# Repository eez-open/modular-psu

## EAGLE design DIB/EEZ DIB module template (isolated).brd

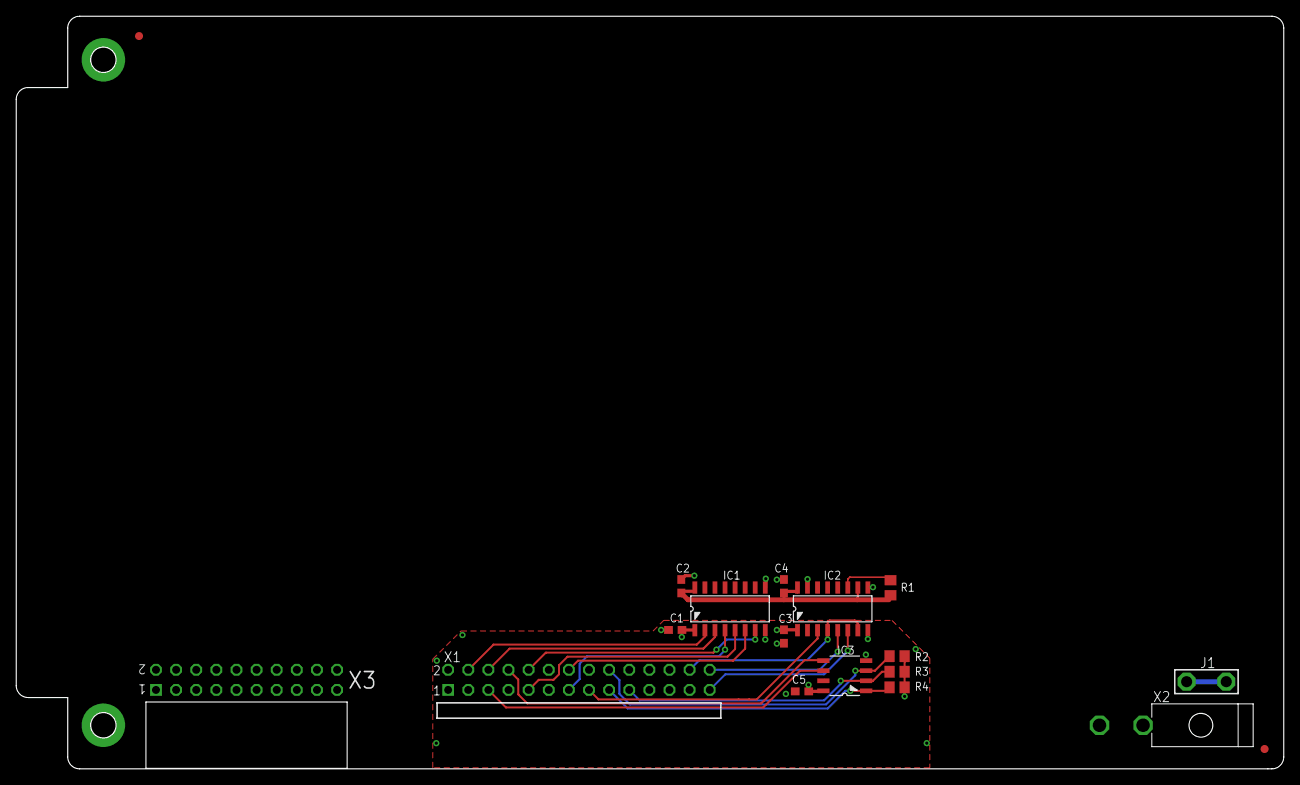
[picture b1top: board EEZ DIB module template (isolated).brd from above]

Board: 4 copper layers, 160.0 x 95.0 mm, 20 parts (0 on the bottom side), 21 nets.

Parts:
C1, C2, C3, C4, C5: 100n; C0603
FM1, FM2: FIDUCIAL_2; FIDUCIAL_DUAL
IC1: Si8662AB-B-IS1; SOIC-16
IC2: Si8641AB-B-IS1; SOIC-16
IC3: M24C32-WMN6P; SOIC127P600X173-8N
J1: 4907; PCB_TAB-4907
KK1, KK2: PMB-1; PCB-MB
R1, R2, R3, R4: 10K; R0805
X1: 77317-104-28LF
X2: 39-30-1020; MINIFIT_39301020
X3: ZL263-20DG; SSW-110-02-T-D-RA

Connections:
+3V3: C2.2, C4.2, IC1.16, IC2.10, IC2.16, R1.2
DIB_A0: IC3.1, R4.2, X1.17
DIB_A1: IC3.2, R3.2, X1.19
DIB_A2: IC3.3, R2.2, X1.18
DIB_BOOT0: IC2.4, IC2.7, X1.26
DIB_CSA: IC1.5, X1.9
DIB_IRQ: IC1.7, X1.10
DIB_MISO: IC1.6, X1.14
DIB_MOSI: IC2.3, X1.15
DIB_NRESET: IC1.2, X1.4
DIB_SCL: IC3.6, X1.5
DIB_SCLK: IC1.4, X1.13
DIB_SDA: IC3.5, X1.8
DIB_SYNC: IC1.3, X1.6
DIB_UART_RX: IC2.6, X1.27
DIB_UART_TX: IC2.5, X1.28
GND: C2.1, C4.1, IC1.9, IC2.9, IC2.15
GNDIO: C1.2, C3.2, C5.1, IC1.8, IC2.2, IC2.8, IC3.4, IC3.7, X1.7, X1.11, X1.16, X1.20, X1.25
PE: J1.1, J1.2
UART_TX: IC2.11, R1.1
V+: C1.1, C3.1, C5.2, IC1.1, IC2.1, IC3.8, R2.1, R3.1, R4.1, X1.1

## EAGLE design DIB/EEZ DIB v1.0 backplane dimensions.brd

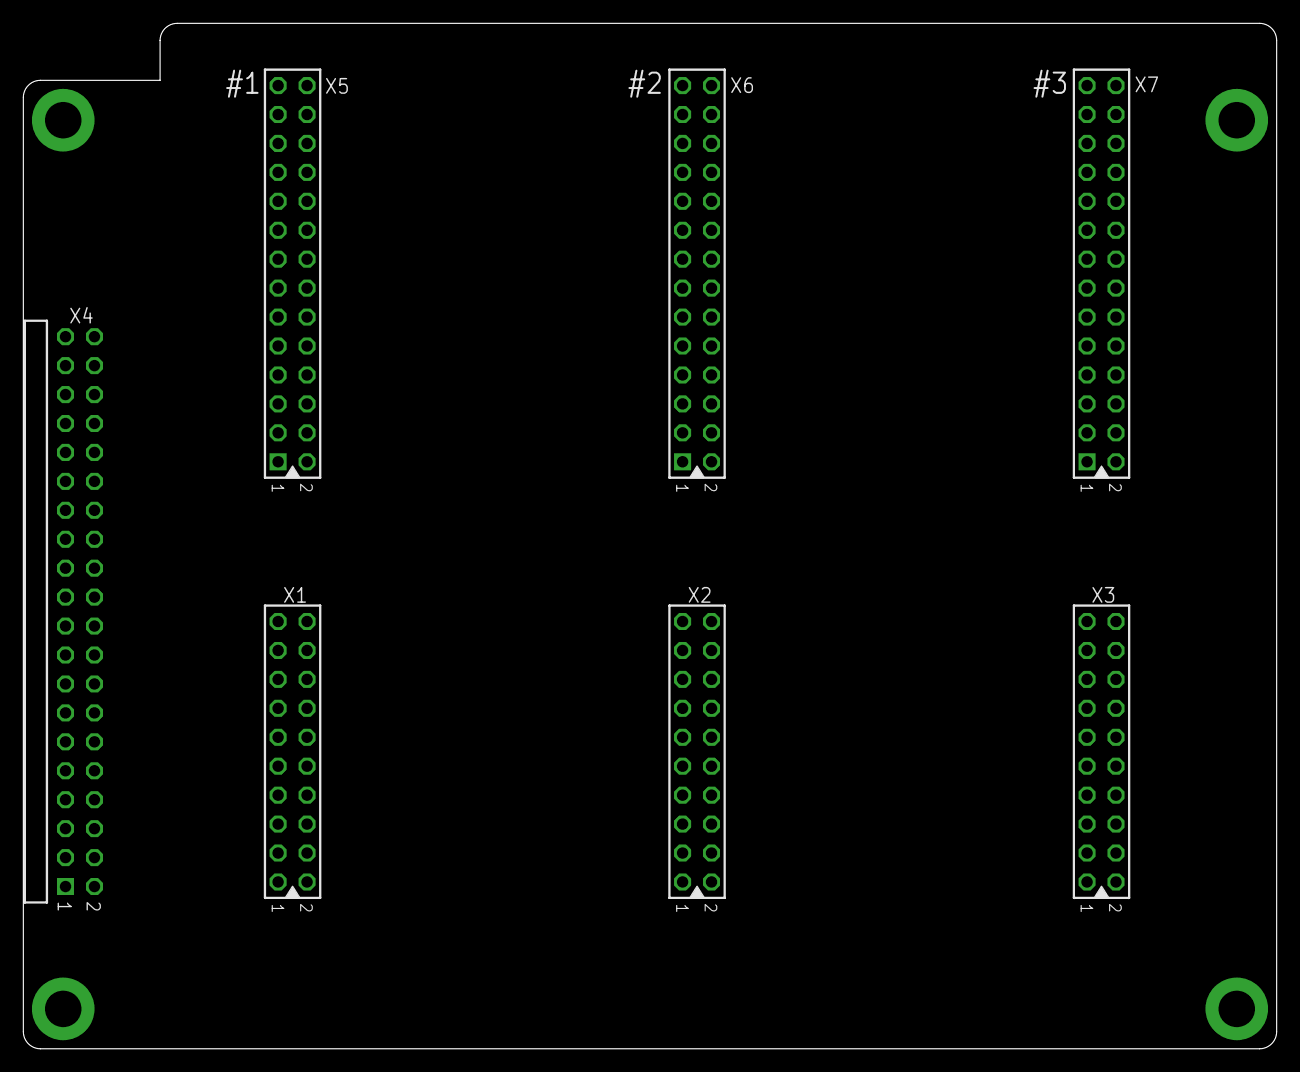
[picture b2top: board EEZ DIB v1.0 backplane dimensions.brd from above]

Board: 2 copper layers, 110.0 x 90.0 mm, 7 parts (0 on the bottom side), 12 nets, no tracks yet.

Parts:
X1, X2, X3: ZL202-20G; DS1021-2*10SF11
X4: ZL212-40KG
X5, X6, X7: TSW-114-07-F-D

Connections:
CH1_IN+: X1.6, X1.7, X1.8, X1.9, X1.10
CH1_OUT+: X1.1, X1.2, X1.3, X1.4, X1.5
CH2_OUT+: X2.1, X2.2, X2.3, X2.4, X2.5
CH3+: X3.1, X3.2, X3.3, X3.4, X3.5
CH3-: X3.16, X3.17, X3.18, X3.19, X3.20
unnamed: X2.16, X2.17, X2.18, X2.19, X2.20
unnamed: X3.6, X3.7, X3.8, X3.9, X3.10
unnamed: X3.11, X3.12, X3.13, X3.14, X3.15
unnamed: X1.16, X1.17, X1.18, X1.19, X1.20
unnamed: X1.11, X1.12, X1.13, X1.14, X1.15
unnamed: X2.11, X2.12, X2.13, X2.14, X2.15
unnamed: X2.6, X2.7, X2.8, X2.9, X2.10

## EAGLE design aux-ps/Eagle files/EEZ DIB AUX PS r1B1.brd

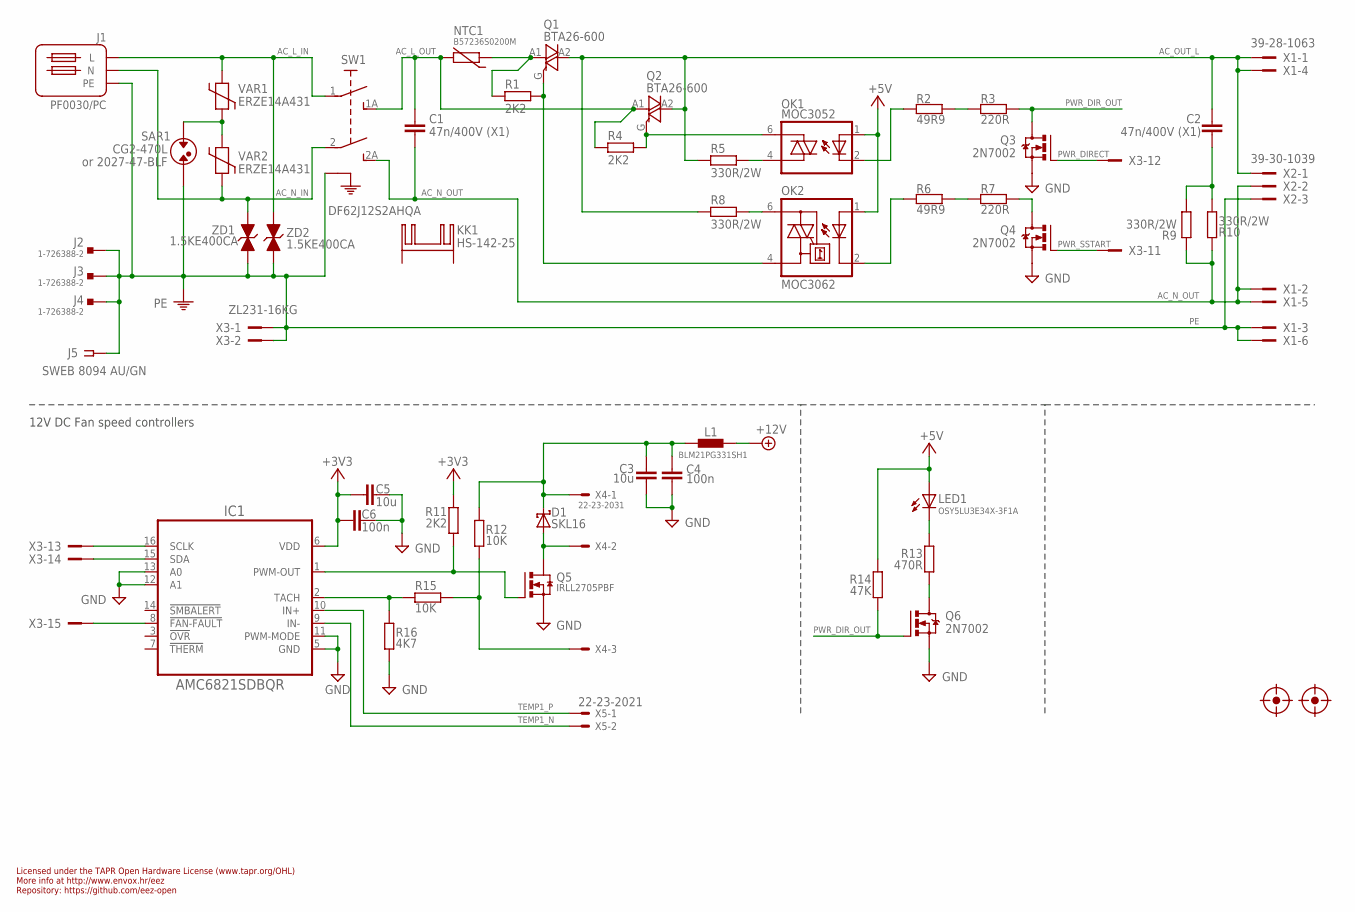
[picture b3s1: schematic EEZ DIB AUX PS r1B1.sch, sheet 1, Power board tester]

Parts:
C1, C2: 47n/400V (X1); C102-054X133
C3, C5: 10u; C1206
C4, C6: 100n; C0603
D1: SKL16; SOD123
FM1, FM2: FIDUCIAL
IC1: AMC6821SDBQR; DBQ16
J1: PF0030/PC
J2, J3, J4: 1-726388-2; PCB_TAB-4.8MM
J5: SWEB 8094 AU/GN; S16N-PC
KK1: HS-142-25; SK129
L1: BLM21PG331SH1; 0805
LED1: OSY5LU3E34X-3F1A; OSG8
NTC1: B57236S0200M; NTC_11.5X6_RM5
OK1: MOC3052; DIL6-SMD
OK2: MOC3062; DIL6-SMD; MPN MOC3033S-M
Q1, Q2: BTA26-600; TOP3S-1
Q3, Q4: 2N7002; SOT103P240X110-3N
Q5: IRLL2705PBF; SOT223
Q6: 2N7002; SOT103P240X110-3N; MPN 2N7002-7-F
R1, R4, R11: 2K2; R0805
R2, R6: 49R9; R0805
R3, R7: 220R; R0805
R5, R8, R9, R10: 330R/2W; R2512
R12, R15: 10K; R0805
R13: 470R; R0805
R14: 47K; R0805
R16: 4K7; R0805
SAR1: CG2-470L; SAR
SW1: DF62J12S2AHQA; DF62J12S2
VAR1, VAR2: ERZE14A431; VARISTOR_13MM
X1: 39-28-1063; MINIFIT_5566-06A_CRE
X2: 39-30-1039; MINIFIT_39301039_CRE
X3: ZL231-16KG; ML16L
X4: 22-23-2031
X5: 22-23-2021
ZD1, ZD2: 1.5KE400CA; DO201-BIDIR

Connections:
+3V3: C5.2, C6.2, IC1.6 (VDD), R11.1; also elsewhere on the board
+5V: LED1.A, OK1.1 (A), OK2.1 (A), R14.1; also elsewhere on the board
+12V: L1.2; also elsewhere on the board
AC_L_IN: J1.L, SW1.1, VAR1.2, ZD2.A (2)
AC_L_OUT: C1.1, NTC1.1, Q2.A1, R4.2, SW1.1A (S); also elsewhere on the board
AC_N_IN: J1.N, SW1.2 (P1), VAR2.1, ZD1.A (2)
AC_N_OUT: C1.2, R9.1, R10.1, SW1.2A (S1), X1.2, X1.5, X2.2; also elsewhere on the board
AC_OUT_L: C2.1, Q1.A2, Q2.A2, R5.2, R8.2, X1.1, X1.4, X2.1
FAN_OUT: D1.A, Q5.2 (D), Q5.4 (D), X4.2
FAN_SENSE: R12.1, R15.2, X4.3
unnamed: NTC1.2, Q1.A1, R1.1
unnamed: IC1.2 (TACH), R15.1, R16.1
unnamed: SAR1.P$1, VAR1.1, VAR2.2
unnamed: Q6.3 (D), R13.2
unnamed: LED1.C, R13.1
unnamed: Q4.3 (D), R7.2
unnamed: IC1.1 (PWM-OUT), Q5.1 (G), R11.2
unnamed: C3.1, C4.1, D1.C, L1.1, R12.2, X4.1
unnamed: OK1.6 (A2), Q2.G, R4.1
unnamed: OK2.4 (A1), Q1.G, R1.2
unnamed: OK2.6 (A2), R8.1
unnamed: R2.2, R3.1
unnamed: R6.2, R7.1
unnamed: OK1.4 (A1), R5.1
unnamed: C2.2, R9.2, R10.2
unnamed: OK2.2 (C), R6.1
unnamed: OK1.2 (C), R2.1
NFAULT: IC1.8 (!FAN-FAULT), X3.15
PE: J1.PE, J2.P$1, J2.P$2, J3.P$1, J3.P$2, J4.P$1, J4.P$2, J5.1, J5.NC1, J5.NC2, J5.NC3, J5.NC4, SAR1.P$2, SW1.PE1 (PE), SW1.PE2 (PE), X1.3, X1.6, X2.3, X3.1, X3.2, ZD1.C (1), ZD2.C (1); also elsewhere on the board
PWR_DIRECT: Q3.1 (G), X3.12
PWR_DIR_OUT: Q3.3 (D), Q6.1 (G), R3.2, R14.2
PWR_SSTART: Q4.1 (G), X3.11
SSCL: IC1.16 (SCLK), X3.13
SSDA: IC1.15 (SDA), X3.14
TEMP1_N: IC1.9 (IN-), X5.2
TEMP1_P: IC1.10 (IN+), X5.1

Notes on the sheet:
Licensed under the TAPR Open Hardware License (www.tapr.org/OHL)
Repository: https://github.com/eez-open
More info at http://www.envox.hr/eez
or 2027-47-BLF
12V DC Fan speed controllers

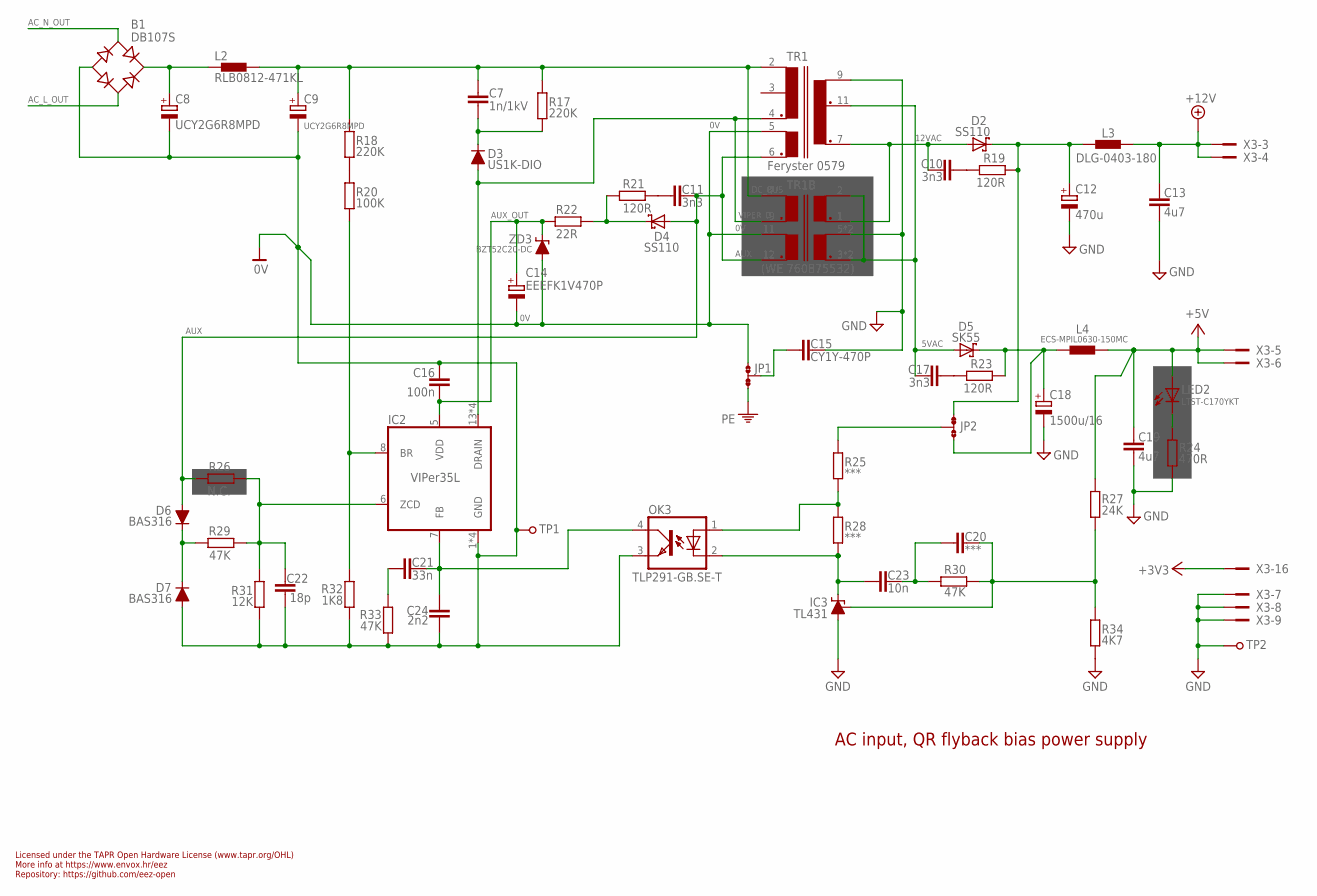
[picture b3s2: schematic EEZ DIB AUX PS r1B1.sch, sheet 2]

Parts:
B1: DB107S; DBS
C7: 1n/1kV; C1210
C8, C9: UCY2G6R8MPD; ECAP5/10.5
C10, C11, C17: 3n3; C0805
C12: 470u; ECAP5/10.5
C13, C19: 4u7; C1206
C14: EEEFK1V470P; CAPAE660X610N
C15: CY1Y-470P; CY075-032X103
C16: 100n; C0603
C18: 1500u/16; ECAP5/13
C20: ***; C0805
C21: 33n; C0805
C22: 18p; C0603
C23: 10n; C0805
C24: 2n2; C0805
D2, D4: SS110; SMB
D3: US1K-DIO; DO214AA
D5: SK55; SMB
D6, D7: BAS316; SOD323-R
IC2: VIPer35L; SOIC-16
IC3: TL431; SOT103P240X110-3N
JP1, JP2: JP3-CUT
L2: RLB0812-471KL; FERSYTER_DSZ6
L3: DLG-0403-180; DE0403
L4: ECS-MPIL0630-150MC; DE0704
LED2: LTST-C170YKT; LED_0805
OK3: TLP291-GB.SE-T; SO4
R17, R18: 220K; R1206
R19, R21, R23: 120R; R0805
R20: 100K; R0805
R22: 22R; R0805
R24: 470R; R0805
R25, R28: ***; R0805
R26: N.C.; R0805
R27: 24K; R0805
R29, R30, R33: 47K; R0805
R31: 12K; R0805
R32: 1K8; R0805
R34: 4K7; R0805
TP1, TP2: PCB_TEST_TABSHIELD; PCB_SHIELD_TAB
TR1: Feryster 0579; FERYSTER_0579
TR1B: (WE 760875532); WE-UOST
X3: ZL231-16KG; ML16L
ZD3: BZT52C20-DC; SOD123

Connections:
5VAC: C17.2, D5.A, TR1.11 (S1_DOT), TR1B.2 (S1), TR1B.3 (S2_DOT), TR1B.4 (S2_DOT)
12VAC: C10.2, D2.A, TR1.7 (S2_DOT), TR1B.1 (S1_DOT)
+3V3: X3.16; also elsewhere on the board
+5V: C19.1, L4.2, LED2.A, R27.2, X3.5, X3.6; also elsewhere on the board
+5V_REC: C18.+, D5.C, JP2.NO, L4.1, R23.1
+12V: C13.1, L3.2, X3.3, X3.4; also elsewhere on the board
+12V_REC: C12.+, D2.C, JP2.NC, L3.1, R19.1
AC_L_OUT: B1.AC2; also elsewhere on the board
AC_N_OUT: B1.AC1; also elsewhere on the board
AUX: C11.2, D4.A, D6.A, R26.2, TR1.6 (AUX_DOT), TR1B.12 (AUX_DOT)
AUX_OUT: C14.1 (+), C16.2, IC2.5 (VDD), R22.2, ZD3.C
AUX_REC: D4.C, R21.1, R22.1
DC_BUS: C7.1, C9.+, L2.P$2 (2), R17.1, R18.1, TR1.2 (P1), TR1B.7 (P1)
FB1: C23.1, IC3.1 (C), OK3.2 (C), R28.2
unnamed: C15.1, JP1.COM
unnamed: OK3.1 (A), R25.2, R28.1
unnamed: C10.1, R19.2
unnamed: B1.+, C8.+, L2.P$1 (1)
unnamed: LED2.C, R24.1
unnamed: JP2.COM, R25.1
unnamed: IC2.8 (BR), R20.2, R32.1
unnamed: R18.2, R20.1
unnamed: C7.2, D3.C, R17.2
unnamed: C21.2, C24.1, IC2.7 (FB), OK3.4 (COL)
unnamed: C11.1, R21.2
unnamed: C22.1, IC2.6 (ZCD), R26.1, R29.1, R31.2
unnamed: C17.1, R23.2
unnamed: C20.2, IC3.2 (REF), R27.1, R30.2, R34.2
unnamed: C20.1, C23.2, R30.1
unnamed: C21.1, R33.1
unnamed: D6.C, D7.C, R29.2
PE: JP1.NC; also elsewhere on the board

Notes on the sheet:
Licensed under the TAPR Open Hardware License (www.tapr.org/OHL)
Repository: https://github.com/eez-open
More info at https://www.envox.hr/eez
AC input, QR flyback bias power supply

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
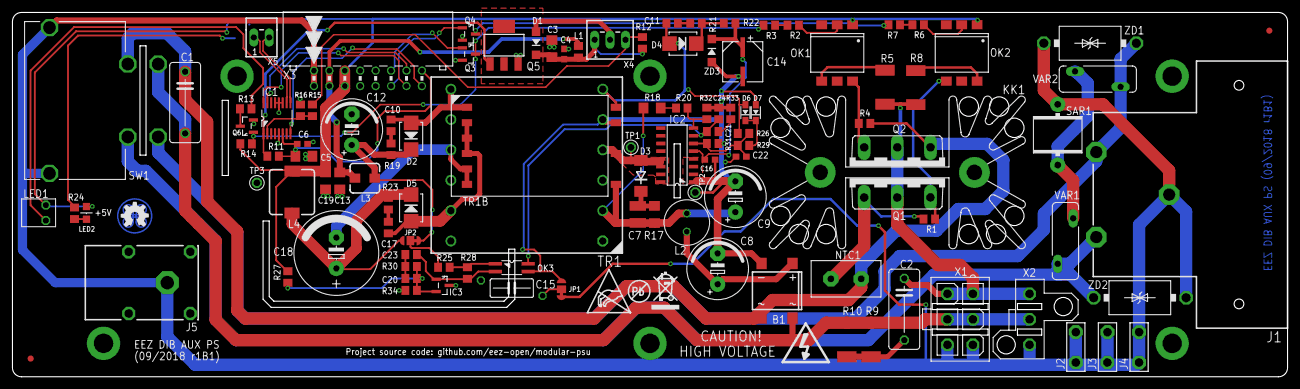
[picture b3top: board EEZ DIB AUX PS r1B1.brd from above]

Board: 2 copper layers, 210.0 x 60.0 mm, 116 parts (0 on the bottom side), 65 nets.

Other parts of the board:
EEZ_SIGNATURE: SIGNATURESMALL; SIGNATURE_5MM
TP3: PCB_SHIELD_TAB
U$2: PB_SMALL
U$3: RECYCLE_BIN1/8
U$4: ESD_SYMBOL

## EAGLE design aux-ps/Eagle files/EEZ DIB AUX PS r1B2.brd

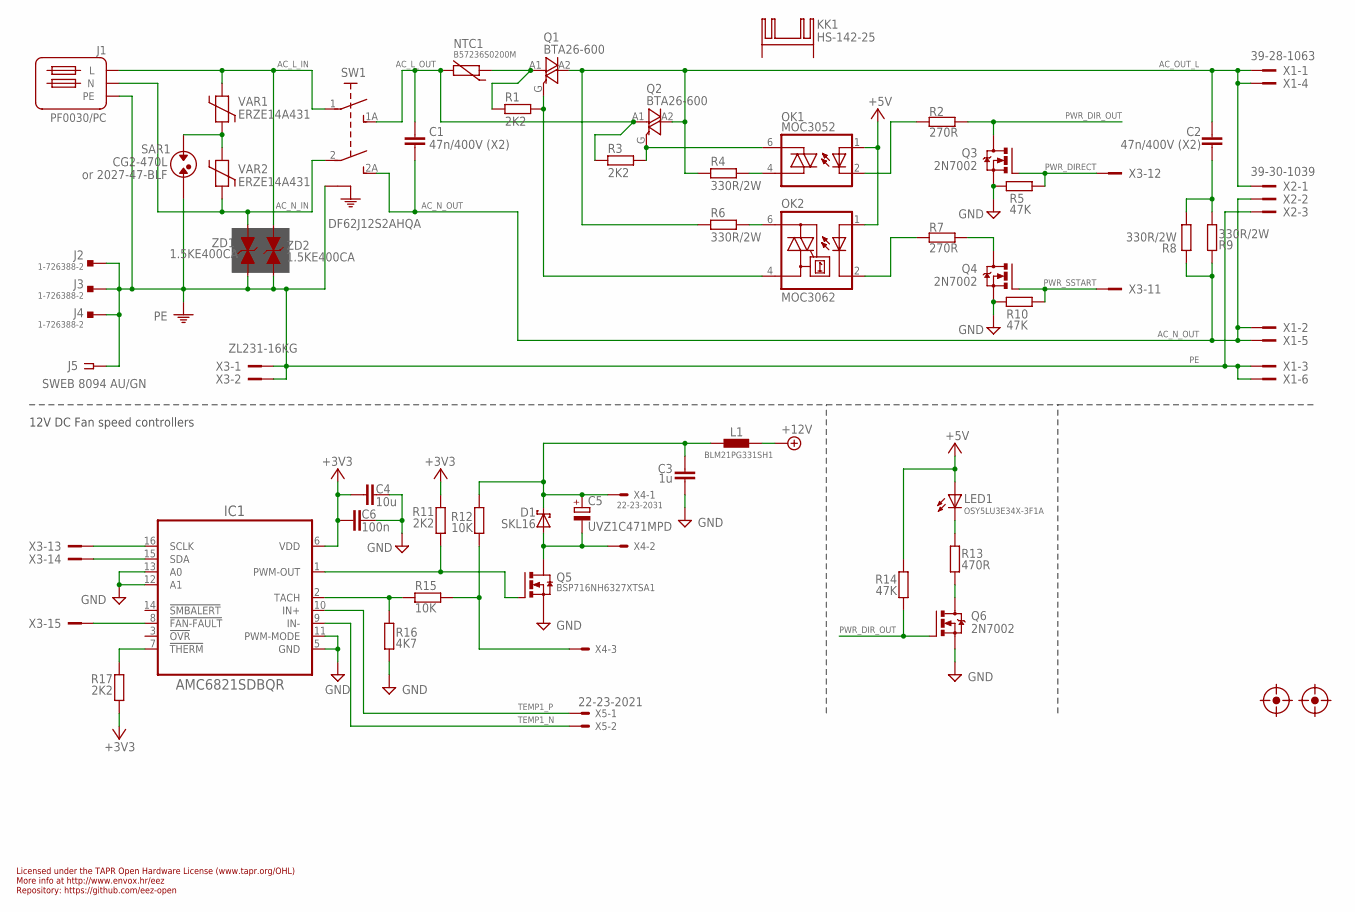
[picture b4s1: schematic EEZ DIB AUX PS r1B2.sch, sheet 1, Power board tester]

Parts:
C1, C2: 47n/400V (X2); C102-054X133
C3: 1u; C0805
C4: 10u; C1206
C5: UVZ1C471MPD; ECAP3.5/8
C6: 100n; C0603
D1: SKL16; SOD123
FM1, FM2: FIDUCIAL
IC1: AMC6821SDBQR; DBQ16
J1: PF0030/PC
J2, J3, J4: 1-726388-2; PCB_TAB-4.8MM
J5: SWEB 8094 AU/GN; S16N-PC
KK1: HS-142-25; SK129
L1: BLM21PG331SH1; 0805
LED1: OSY5LU3E34X-3F1A; OSG8
NTC1: B57236S0200M; NTC_11.5X6_RM5
OK1: MOC3052; DIL6-SMD
OK2: MOC3062; DIL6-SMD; MPN MOC3033S-M
Q1, Q2: BTA26-600; TOP3S-1
Q3, Q4: 2N7002; SOT103P240X110-3N
Q5: BSP716NH6327XTSA1; SOT223
Q6: 2N7002; SOT103P240X110-3N; MPN 2N7002-7-F
R1, R3, R11, R17: 2K2; R0805
R2, R7: 270R; R0805
R4, R6, R8, R9: 330R/2W; R2512
R5, R10, R14: 47K; R0805
R12, R15: 10K; R0805
R13: 470R; R0805
R16: 4K7; R0805
SAR1: CG2-470L; SAR
SW1: DF62J12S2AHQA; DF62J12S2
VAR1, VAR2: ERZE14A431; VARISTOR_13MM
X1: 39-28-1063; MINIFIT_5566-06A_CRE
X2: 39-30-1039; MINIFIT_39301039_CRE
X3: ZL231-16KG; ML16L
X4: 22-23-2031
X5: 22-23-2021
ZD1, ZD2: 1.5KE400CA; DO201-BIDIR

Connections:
+3V3: C4.2, C6.2, IC1.6 (VDD), R11.1, R17.2; also elsewhere on the board
+5V: LED1.A, OK1.1 (A), OK2.1 (A), R14.1; also elsewhere on the board
+12V: L1.2; also elsewhere on the board
+12V_FAN: C3.1, C5.+, D1.C, L1.1, R12.2, X4.1
AC_L_IN: J1.L, SW1.1, VAR1.2, ZD2.A (2)
AC_L_OUT: C1.1, NTC1.1, Q2.A1, R3.2, SW1.1A (S); also elsewhere on the board
AC_N_IN: J1.N, SW1.2 (P1), VAR2.1, ZD1.A (2)
AC_N_OUT: C1.2, R8.1, R9.1, SW1.2A (S1), X1.2, X1.5, X2.2; also elsewhere on the board
AC_OUT_L: C2.1, Q1.A2, Q2.A2, R4.2, R6.2, X1.1, X1.4, X2.1
FAN_OUT: C5.-, D1.A, Q5.2 (D), Q5.4 (D), X4.2
FAN_SENSE: R12.1, R15.2, X4.3
GND: C3.2, C4.1, C6.1, IC1.5 (GND), IC1.11 (PWM-MODE), IC1.12 (A1), IC1.13 (A0), Q3.2 (S), Q4.2 (S), Q5.3 (S), Q6.2 (S), R5.1, R10.1, R16.2; also elsewhere on the board
unnamed: NTC1.2, Q1.A1, R1.1
unnamed: IC1.2 (TACH), R15.1, R16.1
unnamed: IC1.7 (!THERM), R17.1
unnamed: SAR1.P$1, VAR1.1, VAR2.2
unnamed: OK2.2 (C), R7.1
unnamed: OK1.2 (C), R2.1
unnamed: Q6.3 (D), R13.2
unnamed: LED1.C, R13.1
unnamed: Q4.3 (D), R7.2
unnamed: IC1.1 (PWM-OUT), Q5.1 (G), R11.2
unnamed: OK1.6 (A2), Q2.G, R3.1
unnamed: OK2.4 (A1), Q1.G, R1.2
unnamed: OK2.6 (A2), R6.1
unnamed: OK1.4 (A1), R4.1
unnamed: C2.2, R8.2, R9.2
NFAULT: IC1.8 (!FAN-FAULT), X3.15
PE: J1.PE, J2.P$1, J2.P$2, J3.P$1, J3.P$2, J4.P$1, J4.P$2, J5.1, J5.NC1, J5.NC2, J5.NC3, J5.NC4, SAR1.P$2, SW1.PE1 (PE), SW1.PE2 (PE), X1.3, X1.6, X2.3, X3.1, X3.2, ZD1.C (1), ZD2.C (1); also elsewhere on the board
PWR_DIRECT: Q3.1 (G), R5.2, X3.12
PWR_DIR_OUT: Q3.3 (D), Q6.1 (G), R2.2, R14.2
PWR_SSTART: Q4.1 (G), R10.2, X3.11
SSCL: IC1.16 (SCLK), X3.13
SSDA: IC1.15 (SDA), X3.14
TEMP1_N: IC1.9 (IN-), X5.2
TEMP1_P: IC1.10 (IN+), X5.1

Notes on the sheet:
Licensed under the TAPR Open Hardware License (www.tapr.org/OHL)
Repository: https://github.com/eez-open
More info at http://www.envox.hr/eez
or 2027-47-BLF
12V DC Fan speed controllers

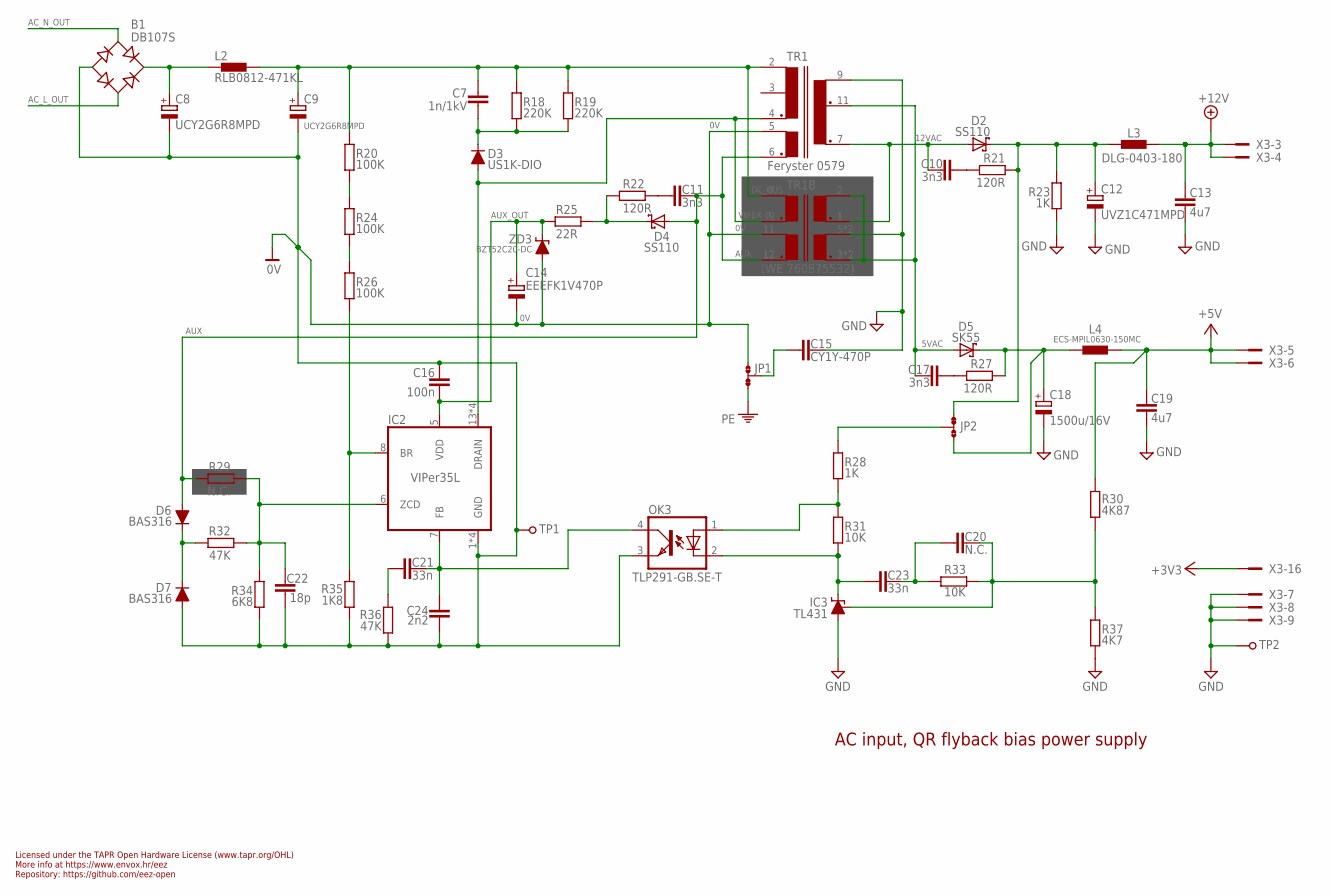
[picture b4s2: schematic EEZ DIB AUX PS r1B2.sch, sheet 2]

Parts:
B1: DB107S; DBS
C7: 1n/1kV; C1210
C8, C9: UCY2G6R8MPD; ECAP5/10.5
C10, C11, C17: 3n3; C0805
C12: UVZ1C471MPD; ECAP3.5/8
C13, C19: 4u7; C1210
C14: EEEFK1V470P; CAPAE660X610N
C15: CY1Y-470P; CY075-032X103
C16: 100n; C0603
C18: 1500u/16V; ECAP5/13
C20: N.C.; C0805
C21, C23: 33n; C0805
C22: 18p; C0603
C24: 2n2; C0805
D2, D4: SS110; SMB
D3: US1K-DIO; DO214AA
D5: SK55; SMB
D6, D7: BAS316; SOD323-R
IC2: VIPer35L; SOIC-16
IC3: TL431; SOT103P240X110-3N
JP1, JP2: JP3-CUT
L2: RLB0812-471KL; FERSYTER_DSZ6
L3: DLG-0403-180; DE0403
L4: ECS-MPIL0630-150MC; DE0704
OK3: TLP291-GB.SE-T; SO4
R18, R19: 220K; R1206
R20, R24, R26: 100K; R1206
R21, R22, R27: 120R; R0805
R23, R28: 1K; R0805
R25: 22R; R0805
R29: N.C.; R0805
R30: 4K87; R0805
R31, R33: 10K; R0805
R32, R36: 47K; R0805
R34: 6K8; R0805
R35: 1K8; R0805
R37: 4K7; R0805
TP1, TP2: PCB_TEST_TABSHIELD; PCB_SHIELD_TAB
TR1: Feryster 0579; FERYSTER_0579
TR1B: (WE 760875532); WE-UOST
X3: ZL231-16KG; ML16L
ZD3: BZT52C20-DC; SOD123

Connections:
0V: B1.-, C8.-, C9.-, C14.2 (-), C16.1, C22.2, C24.2, D7.A, IC2.1 (GND), IC2.2 (GND), IC2.3 (GND), IC2.4 (GND), JP1.NO, OK3.3 (EMIT), R34.1, R35.2, R36.2, TP1.1, TR1.5 (AUX), TR1B.11 (AUX), ZD3.A
5VAC: C17.2, D5.A, TR1.11 (S1_DOT), TR1B.2 (S1), TR1B.3 (S2_DOT), TR1B.4 (S2_DOT)
12VAC: C10.2, D2.A, TR1.7 (S2_DOT), TR1B.1 (S1_DOT)
+3V3: X3.16; also elsewhere on the board
+5V: C19.1, L4.2, R30.2, X3.5, X3.6; also elsewhere on the board
+5V_REC: C18.+, D5.C, JP2.NO, L4.1, R27.1
+12V: C13.1, L3.2, X3.3, X3.4; also elsewhere on the board
+12V_REC: C12.+, D2.C, JP2.NC, L3.1, R21.1, R23.1
AC_L_OUT: B1.AC2; also elsewhere on the board
AC_N_OUT: B1.AC1; also elsewhere on the board
AUX: C11.2, D4.A, D6.A, R29.2, TR1.6 (AUX_DOT), TR1B.12 (AUX_DOT)
AUX_OUT: C14.1 (+), C16.2, IC2.5 (VDD), R25.2, ZD3.C
AUX_REC: D4.C, R22.1, R25.1
DC_BUS: C7.1, C9.+, L2.P$2 (2), R18.1, R19.1, R20.1, TR1.2 (P1), TR1B.7 (P1)
FB1: C23.1, IC3.1 (C), OK3.2 (C), R31.2
GND: C12.-, C13.2, C15.2, C18.-, C19.2, IC3.3 (A), R23.2, R37.1, TP2.1, TR1.9 (S_COMM), TR1B.5 (S2), TR1B.6 (S2), X3.7, X3.8, X3.9; also elsewhere on the board
unnamed: C15.1, JP1.COM
unnamed: OK3.1 (A), R28.2, R31.1
unnamed: C10.1, R21.2
unnamed: B1.+, C8.+, L2.P$1 (1)
unnamed: R24.2, R26.1
unnamed: JP2.COM, R28.1
unnamed: IC2.8 (BR), R26.2, R35.1
unnamed: R20.2, R24.1
unnamed: C7.2, D3.C, R18.2, R19.2
unnamed: C21.2, C24.1, IC2.7 (FB), OK3.4 (COL)
unnamed: C11.1, R22.2
unnamed: C22.1, IC2.6 (ZCD), R29.1, R32.1, R34.2
unnamed: C17.1, R27.2
unnamed: C20.2, IC3.2 (REF), R30.1, R33.2, R37.2
unnamed: C20.1, C23.2, R33.1
unnamed: C21.1, R36.1
unnamed: D6.C, D7.C, R32.2
PE: JP1.NC; also elsewhere on the board
VIPER_D: D3.A, IC2.13 (DRAIN), IC2.14 (DRAIN), IC2.15 (DRAIN), IC2.16 (DRAIN), TR1.4 (P1_DOT), TR1B.9 (P1_DOT)

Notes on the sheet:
Licensed under the TAPR Open Hardware License (www.tapr.org/OHL)
Repository: https://github.com/eez-open
More info at https://www.envox.hr/eez
AC input, QR flyback bias power supply

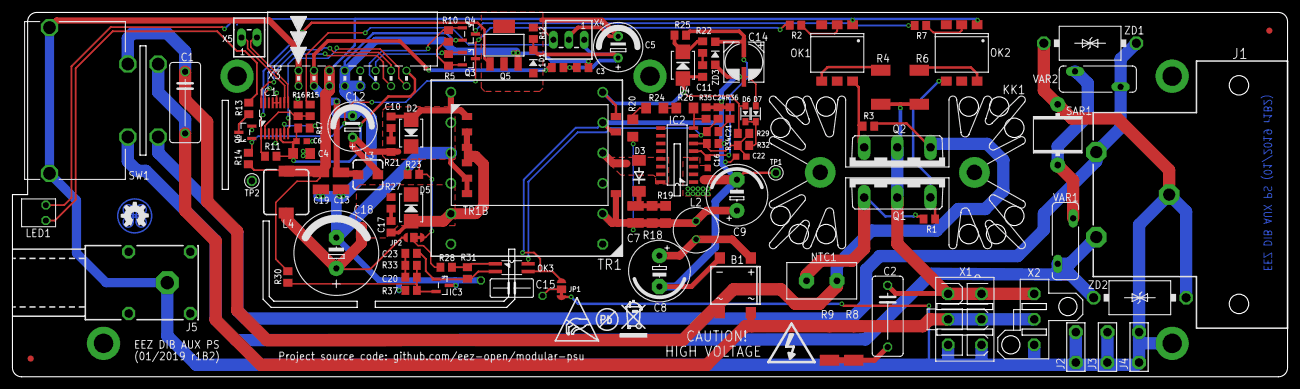
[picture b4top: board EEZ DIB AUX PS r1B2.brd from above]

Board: 2 copper layers, 210.0 x 60.0 mm, 117 parts (0 on the bottom side), 64 nets.

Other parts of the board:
EEZ_SIGNATURE: SIGNATURESMALL; SIGNATURE_5MM
U$2: PB_SMALL
U$3: RECYCLE_BIN1/8
U$4: ESD_SYMBOL

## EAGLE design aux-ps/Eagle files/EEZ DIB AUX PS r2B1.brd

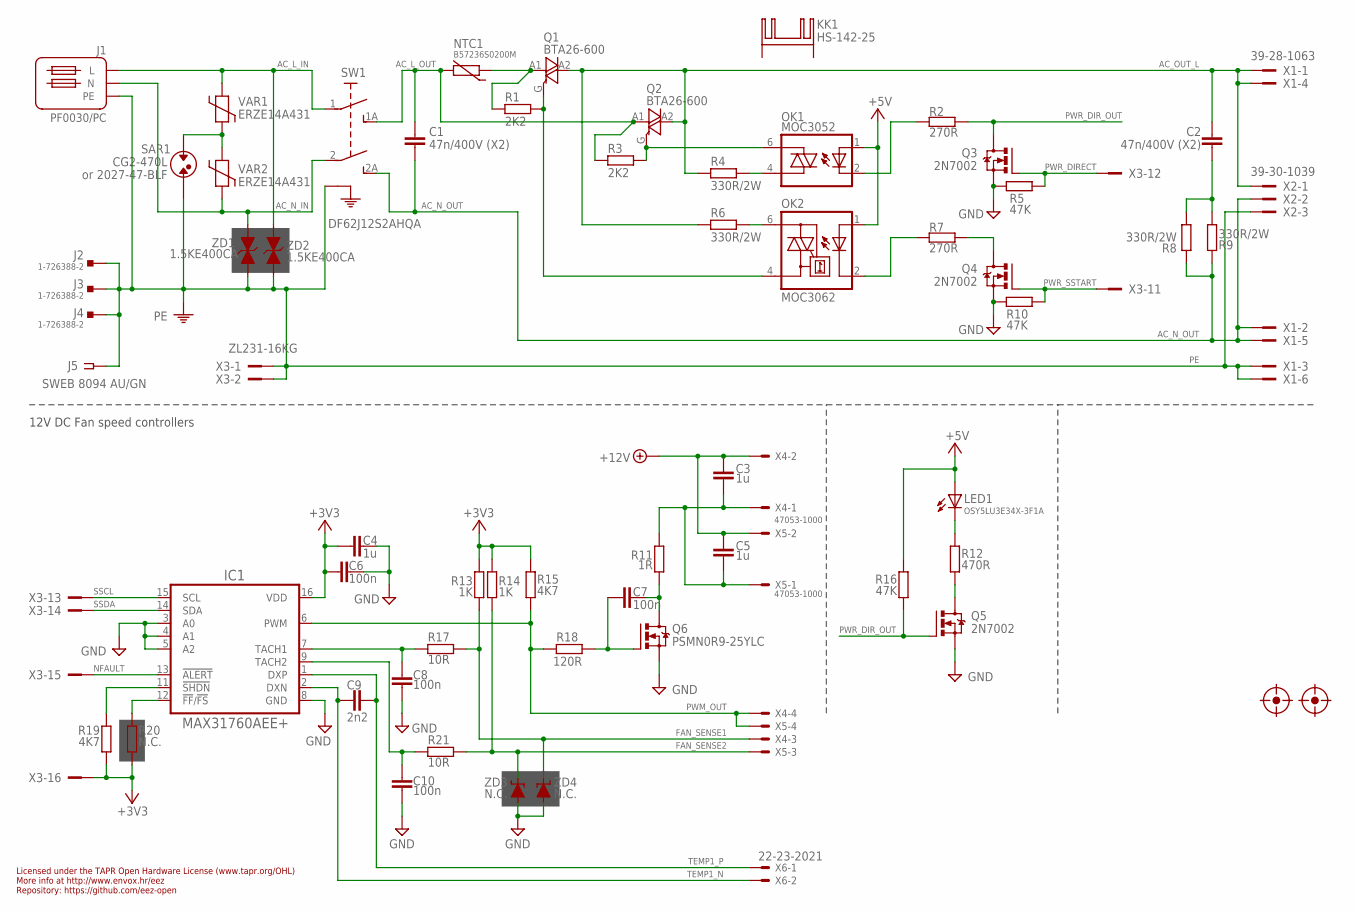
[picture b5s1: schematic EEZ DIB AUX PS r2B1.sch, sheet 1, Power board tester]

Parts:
C1, C2: 47n/400V (X2); C102-054X133
C3, C4, C5: 1u; C0805
C6, C8, C10: 100n; C0603
C7: 100n; C0805
C9: 2n2; C0805
FM1, FM2: FIDUCIAL
IC1: MAX31760AEE+; DBQ16
J1: PF0030/PC
J2, J3, J4: 1-726388-2; PCB_TAB-4.8MM
J5: SWEB 8094 AU/GN; S16N-PC
KK1: HS-142-25; SK129
LED1: OSY5LU3E34X-3F1A; OSG8
NTC1: B57236S0200M; NTC_11.5X6_RM5
OK1: MOC3052; DIL6-SMD
OK2: MOC3062; DIL6-SMD; MPN MOC3033S-M
Q1, Q2: BTA26-600; TOP3S-1
Q3, Q4: 2N7002; SOT103P240X110-3N
Q5: 2N7002; SOT103P240X110-3N; MPN 2N7002-7-F
Q6: PSMN0R9-25YLC; SOT669
R1, R3: 2K2; R0805
R2, R7: 270R; R0805
R4, R6, R8, R9: 330R/2W; R2512
R5, R10, R16: 47K; R0805
R11: 1R; R0805
R12: 470R; R0805
R13, R14: 1K; R0805
R15, R19: 4K7; R0805
R17, R21: 10R; R0805
R18: 120R; R0805
R20: N.C.; R0805
SAR1: CG2-470L; SAR
SW1: DF62J12S2AHQA; DF62J12S2
VAR1, VAR2: ERZE14A431; VARISTOR_13MM
X1: 39-28-1063; MINIFIT_5566-06A_CRE
X2: 39-30-1039; MINIFIT_39301039_CRE
X3: ZL231-16KG; ML16L
X4, X5: 47053-1000
X6: 22-23-2021
ZD1, ZD2: 1.5KE400CA; DO201-BIDIR
ZD3, ZD4: N.C.; SOD123

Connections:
+3V3: C4.2, C6.2, IC1.16 (VDD), R13.2, R14.2, R15.1, R19.2, R20.2, X3.16
+5V: LED1.A, OK1.1 (A), OK2.1 (A), R16.1; also elsewhere on the board
+12V: C3.1, C5.1, X4.2, X5.2; also elsewhere on the board
AC_L_IN: J1.L, SW1.1, VAR1.2, ZD2.A (2)
AC_L_OUT: C1.1, NTC1.1, Q2.A1, R3.2, SW1.1A (S); also elsewhere on the board
AC_N_IN: J1.N, SW1.2 (P1), VAR2.1, ZD1.A (2)
AC_N_OUT: C1.2, R8.1, R9.1, SW1.2A (S1), X1.2, X1.5, X2.2; also elsewhere on the board
AC_OUT_L: C2.1, Q1.A2, Q2.A2, R4.2, R6.2, X1.1, X1.4, X2.1
DRAIN: C7.1, Q6.MB (D), R11.1
FAN_OUT: C3.2, C5.2, R11.2, X4.1, X5.1
FAN_SENSE1: R13.1, R17.2, X4.3, ZD4.C
FAN_SENSE2: R14.1, R21.2, X5.3, ZD3.C
GND: C4.1, C6.1, C8.2, C10.2, IC1.3 (A0), IC1.4 (A1), IC1.5 (A2), IC1.8 (GND), Q3.2 (S), Q4.2 (S), Q5.2 (S), Q6.1 (S), Q6.2 (S), Q6.3 (S), R5.1, R10.1, ZD3.A, ZD4.A; also elsewhere on the board
unnamed: NTC1.2, Q1.A1, R1.1
unnamed: C8.1, IC1.7 (TACH1), R17.1
unnamed: IC1.12 (!FF!/!FS!), R20.1
unnamed: SAR1.P$1, VAR1.1, VAR2.2
unnamed: OK2.2 (C), R7.1
unnamed: OK1.2 (C), R2.1
unnamed: Q5.3 (D), R12.2
unnamed: LED1.C, R12.1
unnamed: C7.2, Q6.4 (G), R18.2
unnamed: Q4.3 (D), R7.2
unnamed: IC1.11 (!SHDN), R19.1
unnamed: C10.1, IC1.9 (TACH2), R21.1
unnamed: OK1.6 (A2), Q2.G, R3.1
unnamed: OK2.4 (A1), Q1.G, R1.2
unnamed: OK2.6 (A2), R6.1
unnamed: OK1.4 (A1), R4.1
unnamed: C2.2, R8.2, R9.2
NFAULT: IC1.13 (!ALERT), X3.15
PE: J1.PE, J2.P$1, J2.P$2, J3.P$1, J3.P$2, J4.P$1, J4.P$2, J5.1, J5.NC1, J5.NC2, J5.NC3, J5.NC4, SAR1.P$2, SW1.PE1 (PE), SW1.PE2 (PE), X1.3, X1.6, X2.3, X3.1, X3.2, ZD1.C (1), ZD2.C (1); also elsewhere on the board
PWM_OUT: IC1.6 (PWM), R15.2, R18.1, X4.4, X5.4
PWR_DIRECT: Q3.1 (G), R5.2, X3.12
PWR_DIR_OUT: Q3.3 (D), Q5.1 (G), R2.2, R16.2
PWR_SSTART: Q4.1 (G), R10.2, X3.11
SSCL: IC1.15 (SCL), X3.13
SSDA: IC1.14 (SDA), X3.14
TEMP1_N: C9.2, IC1.2 (DXN), X6.2
TEMP1_P: C9.1, IC1.1 (DXP), X6.1

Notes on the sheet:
Licensed under the TAPR Open Hardware License (www.tapr.org/OHL)
Repository: https://github.com/eez-open
More info at http://www.envox.hr/eez
or 2027-47-BLF
12V DC Fan speed controllers

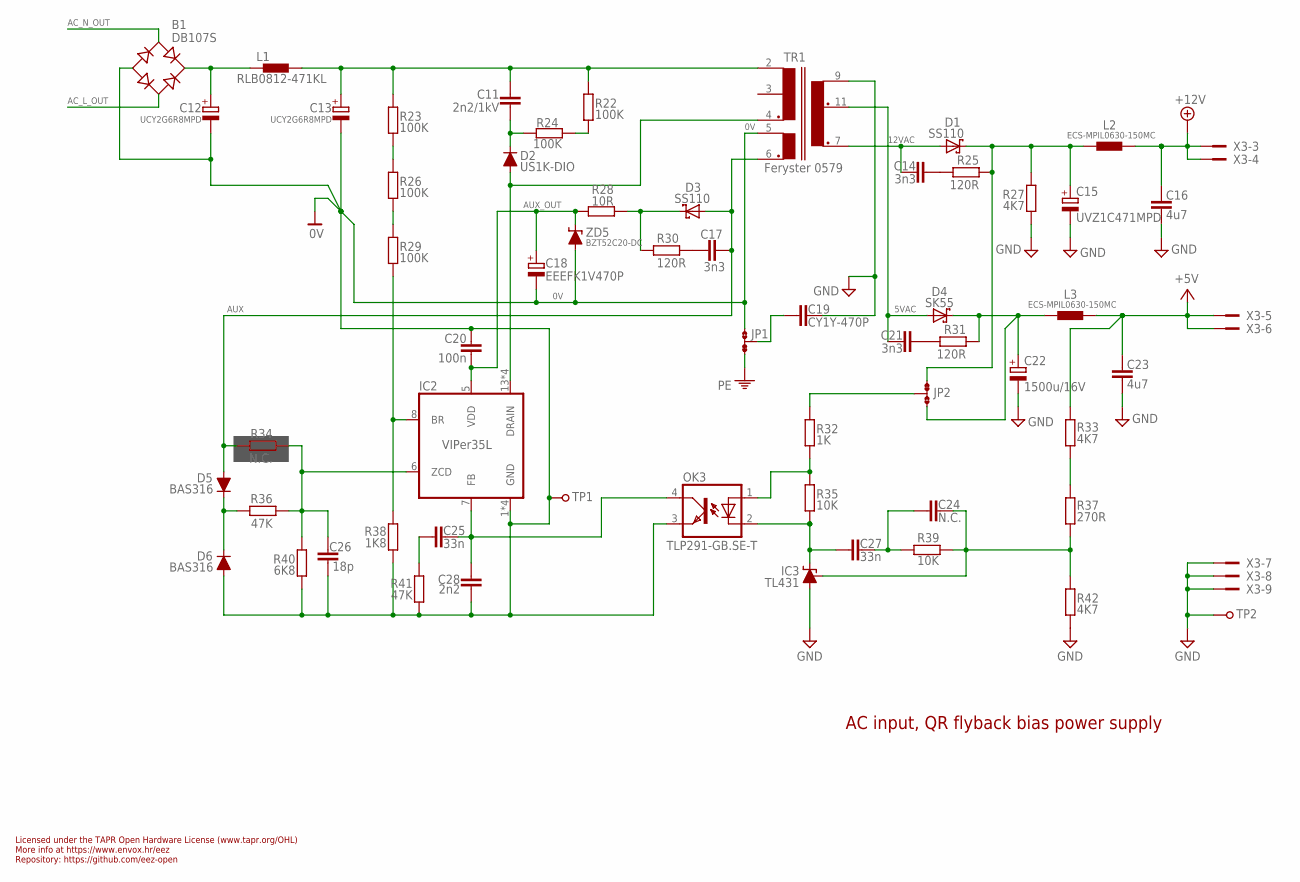
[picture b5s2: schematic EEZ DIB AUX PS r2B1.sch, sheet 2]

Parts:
B1: DB107S; DBS
C11: 2n2/1kV; C1210
C12, C13: UCY2G6R8MPD; ECAP5/10.5
C14, C17, C21: 3n3; C0805
C15: UVZ1C471MPD; ECAP3.5/8
C16, C23: 4u7; C1210
C18: EEEFK1V470P; CAPAE660X610N
C19: CY1Y-470P; CY075-032X103
C20: 100n; C0603
C22: 1500u/16V; ECAP5/13
C24: N.C.; C0805
C25, C27: 33n; C0805
C26: 18p; C0603
C28: 2n2; C0805
D1, D3: SS110; SMB
D2: US1K-DIO; DO214AA
D4: SK55; SMB
D5, D6: BAS316; SOD323-R
IC2: VIPer35L; SOIC-16
IC3: TL431; SOT103P240X110-3N
JP1, JP2: JP3-CUT
L1: RLB0812-471KL; FERSYTER_DSZ6
L2, L3: ECS-MPIL0630-150MC; DE0704
OK3: TLP291-GB.SE-T; SO4
R22, R23, R24, R26, R29: 100K; R1206
R25, R30, R31: 120R; R0805
R27, R33, R42: 4K7; R0805
R28: 10R; R0805
R32: 1K; R0805
R34: N.C.; R0805
R35, R39: 10K; R0805
R36, R41: 47K; R0805
R37: 270R; R0805
R38: 1K8; R0805
R40: 6K8; R0805
TP1, TP2: PCB_TEST_TABSHIELD; PCB_SHIELD_TAB
TR1: Feryster 0579; FERYSTER_0579
X3: ZL231-16KG; ML16L
ZD5: BZT52C20-DC; SOD123

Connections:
0V: B1.-, C12.-, C13.-, C18.2 (-), C20.1, C26.2, C28.2, D6.A, IC2.1 (GND), IC2.2 (GND), IC2.3 (GND), IC2.4 (GND), JP1.NO, OK3.3 (EMIT), R38.2, R40.1, R41.2, TP1.1, TR1.5 (AUX), ZD5.A
5VAC: C21.2, D4.A, TR1.11 (S1_DOT)
12VAC: C14.2, D1.A, TR1.7 (S2_DOT)
+5V: C23.1, L3.2, R33.2, X3.5, X3.6; also elsewhere on the board
+5V_REC: C22.+, D4.C, JP2.NO, L3.1, R31.1
+12V: C16.1, L2.2, X3.3, X3.4; also elsewhere on the board
+12V_REC: C15.+, D1.C, JP2.NC, L2.1, R25.1, R27.1
AC_L_OUT: B1.AC2; also elsewhere on the board
AC_N_OUT: B1.AC1; also elsewhere on the board
AUX: C17.2, D3.A, D5.A, R34.2, TR1.6 (AUX_DOT)
AUX_OUT: C18.1 (+), C20.2, IC2.5 (VDD), R28.2, ZD5.C
AUX_REC: D3.C, R28.1, R30.1
DC_BUS: C11.1, C13.+, L1.P$2 (2), R22.1, R23.1, TR1.2 (P1)
FB1: C27.1, IC3.1 (C), OK3.2 (C), R35.2
GND: C15.-, C16.2, C19.2, C22.-, C23.2, IC3.3 (A), R27.2, R42.1, TP2.1, TR1.9 (S_COMM), X3.7, X3.8, X3.9; also elsewhere on the board
unnamed: C19.1, JP1.COM
unnamed: OK3.1 (A), R32.2, R35.1
unnamed: C14.1, R25.2
unnamed: B1.+, C12.+, L1.P$1 (1)
unnamed: R26.2, R29.1
unnamed: JP2.COM, R32.1
unnamed: R22.2, R24.2
unnamed: IC2.8 (BR), R29.2, R38.1
unnamed: R33.1, R37.2
unnamed: R23.2, R26.1
unnamed: C11.2, D2.C, R24.1
unnamed: C25.2, C28.1, IC2.7 (FB), OK3.4 (COL)
unnamed: C17.1, R30.2
unnamed: C26.1, IC2.6 (ZCD), R34.1, R36.1, R40.2
unnamed: C21.1, R31.2
unnamed: C24.2, IC3.2 (REF), R37.1, R39.2, R42.2
unnamed: C24.1, C27.2, R39.1
unnamed: C25.1, R41.1
unnamed: D5.C, D6.C, R36.2
PE: JP1.NC; also elsewhere on the board
VIPER_D: D2.A, IC2.13 (DRAIN), IC2.14 (DRAIN), IC2.15 (DRAIN), IC2.16 (DRAIN), TR1.4 (P1_DOT)

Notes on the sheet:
Licensed under the TAPR Open Hardware License (www.tapr.org/OHL)
Repository: https://github.com/eez-open
More info at https://www.envox.hr/eez
AC input, QR flyback bias power supply

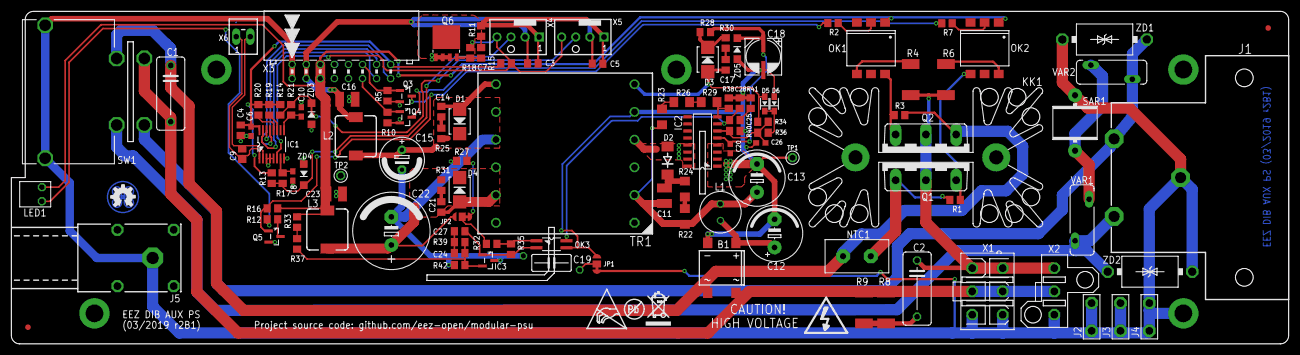
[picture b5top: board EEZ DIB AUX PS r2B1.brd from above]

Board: 2 copper layers, 230.5 x 60.0 mm, 126 parts (0 on the bottom side), 70 nets.

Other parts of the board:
EEZ_SIGNATURE: SIGNATURESMALL; SIGNATURE_5MM
U$2: PB_SMALL
U$3: RECYCLE_BIN1/8
U$4: ESD_SYMBOL

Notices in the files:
parts and their libraries:
EEZ_DIB: This work is licensed under the TAPR Open Hardware License.
